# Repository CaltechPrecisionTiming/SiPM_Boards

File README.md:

# SiPM_Boards
Repository with SiPM PCBs and Instructions

CHOOSING PARTS

Eagle (and generally all schematic/pcb softwares) come with built-in libraries containing some widely-used parts. Most non-specific parts can be found here, so it is useful to check these before either downloading external Eagle libraries from some external internet source or creating your own (which is possible, but painful).

CREATING THE SCHEMATIC

CONVERTING SCHEMATIC TO PCB

SENDING THE PCB TO PRINT

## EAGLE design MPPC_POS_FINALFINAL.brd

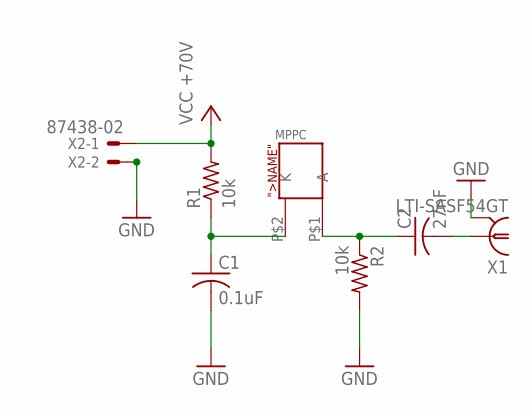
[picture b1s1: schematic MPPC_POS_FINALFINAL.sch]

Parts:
C1: 0.1uF; C1206
C2: 27nF; C1206
R1, R2: 10k; R1206
U$1: MPPC-S12572-025C; MPPC_V2
X1: LTI-SASF54GT
X2: 87438-02

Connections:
GND: C1.2, R2.2, X1.2, X1.3 (2), X1.4 (2), X1.5 (2), X2.2
unnamed: C1.1, R1.1, U$1.P$2 (K)
unnamed: C2.1, R2.1, U$1.P$1 (A)
unnamed: C2.2, X1.1
VCC: R1.2, X2.1

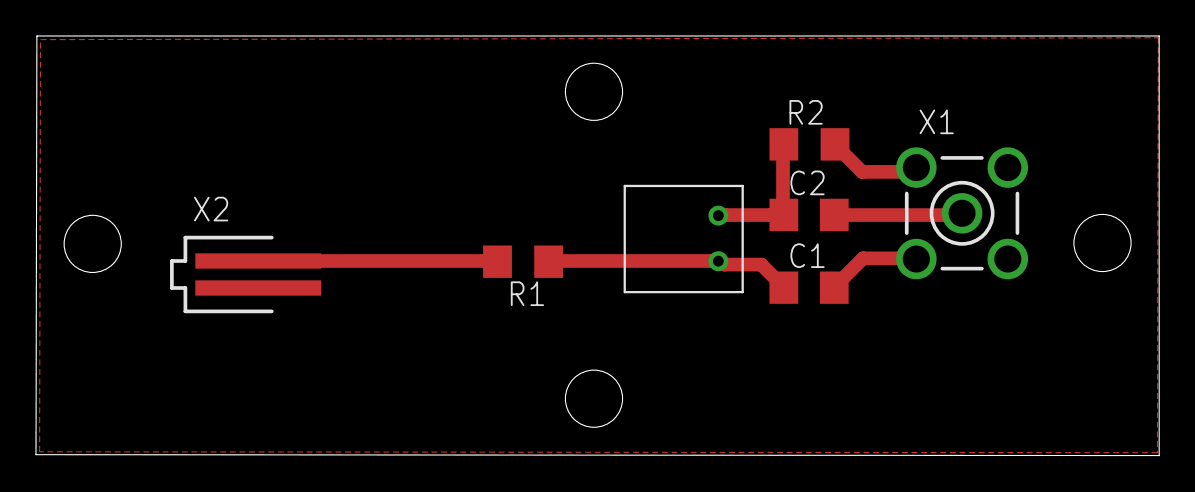
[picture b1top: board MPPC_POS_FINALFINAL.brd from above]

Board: 2 copper layers, 62.4 x 23.3 mm, 7 parts (0 on the bottom side), 5 nets.

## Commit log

2015-04-03 Files including the project, schematic, PCB layout, and picture of the files are included.
2015-04-06 Starting writing out instructions/outline
